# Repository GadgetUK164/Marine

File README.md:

<h1>Marine (Amber Replacement)</h1>
Marine is a modern CPLD replacement, designed to replace the Amber chip in the Commodore Amiga.
This project is based on the work of Matthias Heinrichs - AGA Multifix.
You can see his original project here:- https://gitlab.com/MHeinrichs/multifix-aga/-/tree/master

A massive thanks to Matthias for creating the AGA Multifix, and for allowing me to adapt to an Amber replacement.

<h1>License</h1>
This project is open source, and should not be sold commercially.

Do whatever you want with this, if you do it for private use and mention this work, and the AGA Multifix as origin.
If you want to make money out of this work, ask Matthias Heinrichs.
If you copy parts of this work to your project, mention the source.
If you use parts of this work for closed source, burn in hell and live in fear!

<h1>How Does It Work</h1>
It uses the magic code from the AGA Multifix to control the read resets, write resets, read enables and write enables of the Frame RAM and Line RAM contained on the Amiga 3000 motherboard.  It also works in the GBA1000 from Georg Braun.
JP1 and JP2 are added for future changes.   At the time of public release it supports NTSC Line RAM only.  It may be possible with a future firmware update, to use one of the jumpers to toggle between NTSC and PAL Line RAM.<br><br>   To my knowledge Amiga 3000 computers all shipped with NTSC Line RAM from the factory.  ie. uPD42101.   PAL RAM is uPD42102<br><br>
Note: There are different speeds of these RAM chips.  So far this has been tested working correctly with uPD42101-3 Line RAM.<br>
<ul>
<li>Official 3000 (Rev 9.x)</li>
<li>Re-Amiga 3000 (Rev 11)</li>
<li>GBA1000</li>
</ul>
Note: You could in theory use 2 x PAL Line RAM, and 2 x NTSC Line RAM chips.  The ones on the combined "path" need to be NTSC.<br><br>
In addition J481 on the 3000 motherboard (provided JP1 is closed) can be used to enable scanlines in progressive mode.  Before anyone asks, it's not practical to have scanlines in interlaced modes - additional pixel data is contained in interlaced.  In progressive, each scanline just gets output twice, so a black scanline for the odd scanlines makes sense!<br><br>
<h1>Important</h1>
The board currently fits into the PLCC footprint using turned pins.   It is recommended to remove the PLCC socket, and fit turned pin (female) strips to the motherboard.  Then fit turned pin (male) strips to the Marine PCB.<br><br>
I noticed that when testing PAL Interlaced on the Amiga 3000 using the default 74ALS74 (U480) which Commodore fitted to the motherboard, the video is not very sharp at all.  This can be improved massively by swappping U480 on the 3000 to a 74F74.  The GBA1000 already has a 74F74 in that location.
<br><br>
The RGB output levels to the Commodore Hybrid are at the 3.3v logic levels, and whilst testing has revealed the difference to be a negligble amount of effect on brightness, it may be an idea to fit a customised modern hybrid in place of HY480.
You can alter the bias resistors on a modern Hyrid replacement (eg. to 330 ohm, down from the original 470 ohm).  But in my opinion this is not required.  I've not done it on my 3000, and I honestly cannot see a difference to the output.  If I scope it, I am sure there will be a difference though!<br><br>
As mentioned above, use NTSC Line RAM (uPD42101-3).<br>
In future I might be able to support PAL Line RAM via a code change and use of JP2.

<h1>Repository Contents</h1>
KiCad 7.0 PCB Design Files & Schematics
<br>
ISE 14.7 VHD and pins files for Logic

<h1>Components Needed</h1>
<ul>
<li>Xilinx XC95144XL-10TQ100 CPLD</li>
<li>R1  0603 Resistor 10K</li>
<li>R2  0603 Resistor 10K</li>
<li>R3  0603 Resistor 10K</li>
<li>R4  0603 Resistor 10K</li>
<li>L1  0805 Ferrite (I went with 9ohm @ 100Mhz) - You could just fit 0ohm or 1ohm here I think!</li>
<li>U1  SOT-223 AMS1117 3.3V Regulator</li>
<li>C1  0805 MLC Capacitor 4.7uF 50V</li>
<li>C2  0805 MLC Capacitor 10uF  50V</li>
<li>C3  0805 MLC Capacitor 1uF   50V</li>
<li>C4  0805 MLC Capacitor 100nF 50V</li>
<li>2.54 pitch turned pin strips (female for motherboard, male for Marine)</li>
</ul>

<h1>Limitations</h1>
I offer no warranty on this design.  It works for me, and I am happy!
If you have a problem, I can investigate - but this is a hobby project.<br><br>
Super Hires will display, but not 100% correctly - it can look pretty good but a pixel will be missed every so often due to sampling into smaller RAM at a lower clock rate than required.  The RAM used on the Amiga 3000 cannot hold 1200 pixels of a scanline, so some sampling issues will be noticed when trying to display Super Hires.
I have tested many games and demos that use either interlaced or progressive and found no problems.<br><br>
Video modes supported by Super Denise (ECS) are not supported (as per Amber).
The bypass switch on the 3000 has been tested and works as per Amber original manual bypass.
J481 is not supported as per the original Amber, partly because I couldnt work out how it was used!  It now can be used to enable or disable scanlines in progressive display modes. (JP1 should be closed too enable scan lines - master enable)<br><br>
I found it harder to "dial in" regards the Amiga 3000 PLL adjustment (trim cap and resistor).  That was NOT the case with the Re-Amiga 3000, or the GBA1000.  PLL adjustment on those systems was much easier for me. <br><br>
NTSC interlaced display modes are definitely sharper than PAL interlaced ones, just marginally!  This could indicate that my timing is not spot on just yet!<br><br>
It may benefit from a re-design to add:-<br>
<br>
<ul>
<li>More decoupling on CPLD power pins?</li>
<li>Buffering of RGB output to TTL levels?</li>
<li>Schmitt Triggers on 14Mhz and 28Mhz inputs?</li>
<li>4 layer?</li>
<li>PLCC plug (separate interposer might be possible)?</li>
</ul>

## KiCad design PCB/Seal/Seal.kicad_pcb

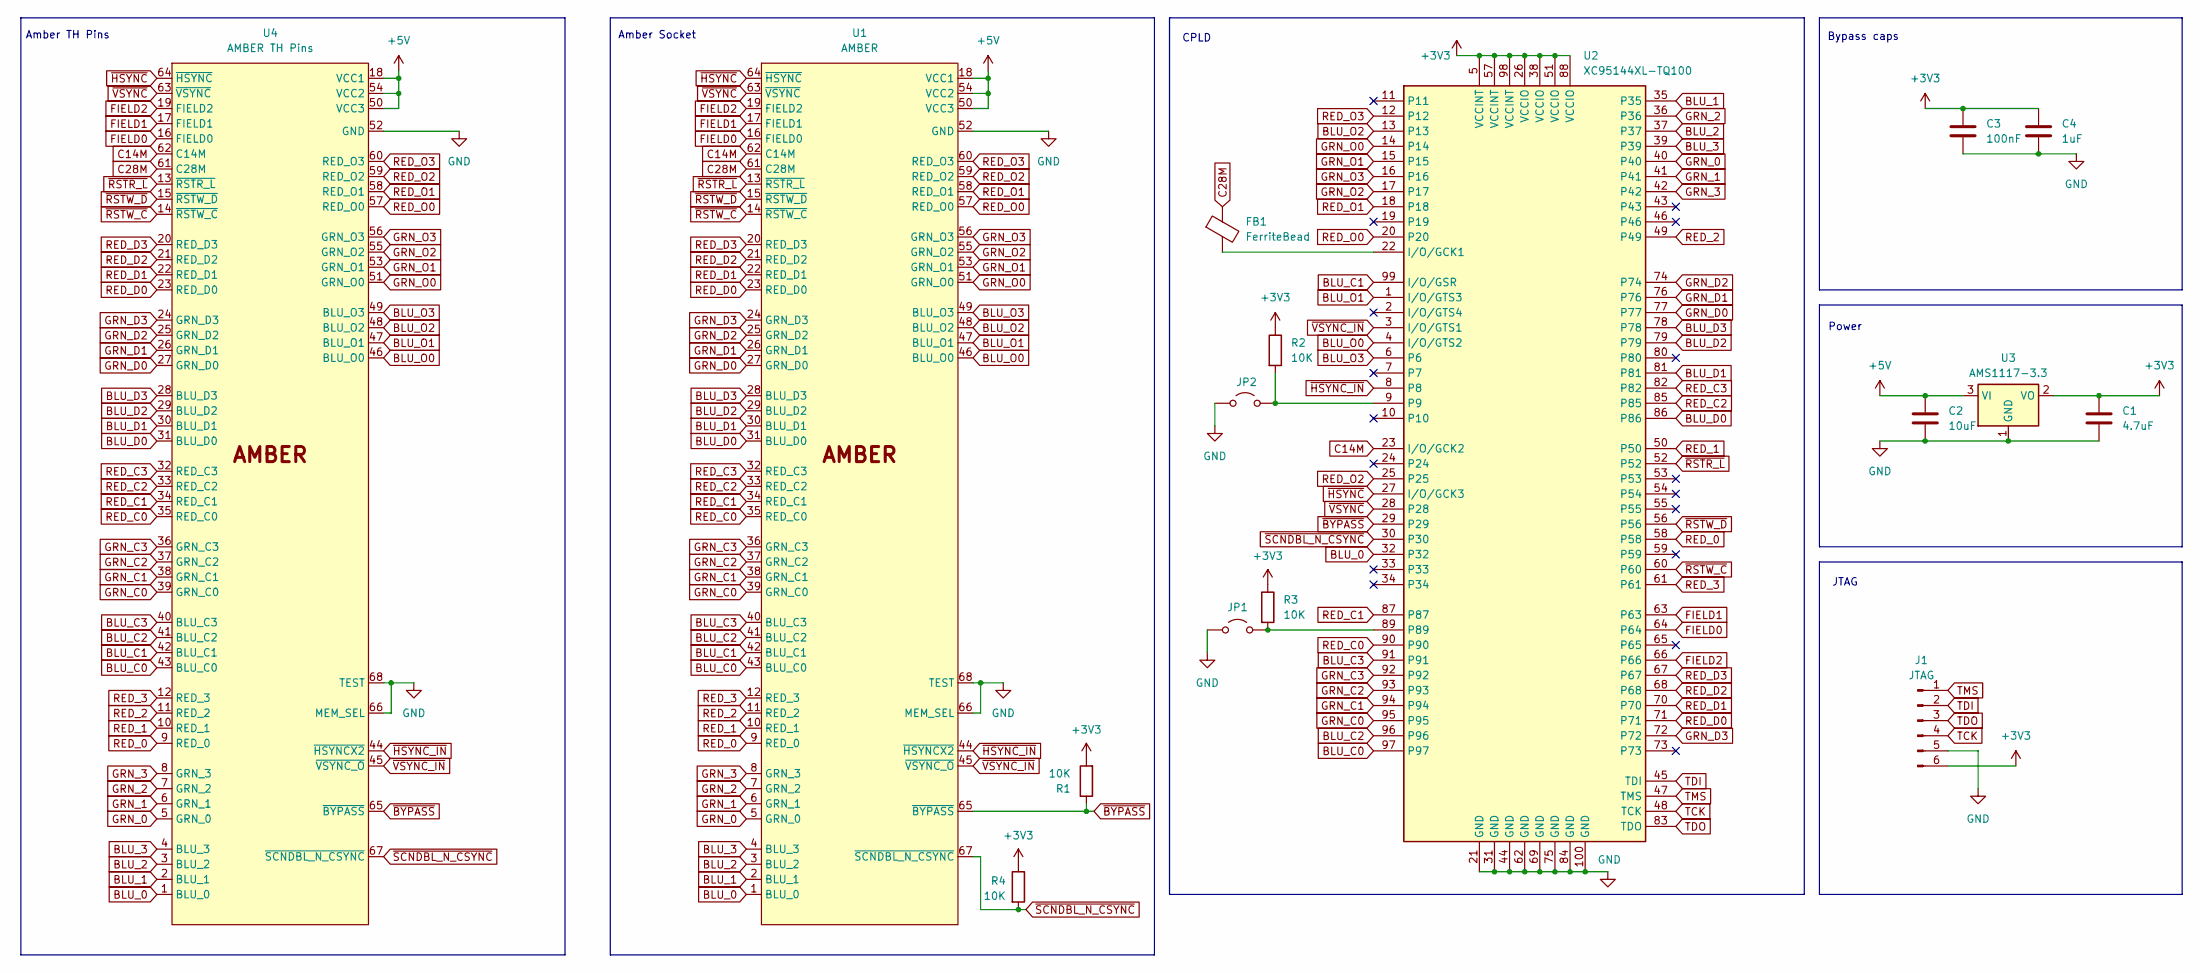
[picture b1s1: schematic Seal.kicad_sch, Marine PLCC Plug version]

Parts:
C1: 4.7uF; C_0603_1608Metric_Pad1.08x0.95mm_HandSolder; LCSC C19666
C2: 10uF; C_0603_1608Metric_Pad1.08x0.95mm_HandSolder; LCSC C96446
C3: 100nF; C_0603_1608Metric_Pad1.08x0.95mm_HandSolder; LCSC C14663
C4: 1uF; C_0603_1608Metric_Pad1.08x0.95mm_HandSolder; LCSC C15849
FB1: FerriteBead; L_0603_1608Metric_Pad1.05x0.95mm_HandSolder; LCSC C88974
J1: JTAG; PinHeader_1x06_P2.54mm_Vertical; LCSC C6332199
JP1, JP2: SolderJumper-2_P1.3mm_Open_RoundedPad1.0x1.5mm
R1, R2, R3, R4: 10K; R_0603_1608Metric_Pad0.98x0.95mm_HandSolder; LCSC C25804
U1: AMBER; APW9327_single_sided
U2: XC95144XL-TQ100; TQFP-100_14x14mm_P0.5mm; LCSC C45126
U3: AMS1117-3.3; SOT-223-3_TabPin2; LCSC C6186
U4: AMBER TH Pins; PLCC-68_TH_pin_holes

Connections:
+3V3: C1.1, C3.1, C4.1, J1.6, R1.2, R2.1, R3.1, R4.1, U2.5 (VCCINT), U2.26 (VCCIO), U2.38 (VCCIO), U2.51 (VCCIO), U2.57 (VCCINT), U2.88 (VCCIO), U2.98 (VCCINT), U3.2 (VO)
+5V: C2.1, U1.18 (VCC1), U1.50 (VCC3), U1.54 (VCC2), U3.3 (VI), U4.18 (VCC1), U4.50 (VCC3), U4.54 (VCC2)
BLU_0: U1.1 (BLU_0), U2.32, U4.1 (BLU_0)
BLU_1: U1.2 (BLU_1), U2.35, U4.2 (BLU_1)
BLU_2: U1.3 (BLU_2), U2.37, U4.3 (BLU_2)
BLU_3: U1.4 (BLU_3), U2.39, U4.4 (BLU_3)
BLU_C0: U1.43 (BLU_C0), U2.97, U4.43 (BLU_C0)
BLU_C1: U1.42 (BLU_C1), U2.99 (I/O/GSR), U4.42 (BLU_C1)
BLU_C2: U1.41 (BLU_C2), U2.96, U4.41 (BLU_C2)
BLU_C3: U1.40 (BLU_C3), U2.91, U4.40 (BLU_C3)
BLU_D0: U1.31 (BLU_D0), U2.86, U4.31 (BLU_D0)
BLU_D1: U1.30 (BLU_D1), U2.81, U4.30 (BLU_D1)
BLU_D2: U1.29 (BLU_D2), U2.79, U4.29 (BLU_D2)
BLU_D3: U1.28 (BLU_D3), U2.78, U4.28 (BLU_D3)
BLU_O0: U1.46 (BLU_O0), U2.4 (I/O/GTS2), U4.46 (BLU_O0)
BLU_O1: U1.47 (BLU_O1), U2.1 (I/O/GTS3), U4.47 (BLU_O1)
BLU_O2: U1.48 (BLU_O2), U2.13, U4.48 (BLU_O2)
BLU_O3: U1.49 (BLU_O3), U2.6, U4.49 (BLU_O3)
C14M: U1.62 (C14M), U2.23 (I/O/GCK2), U4.62 (C14M)
C28M: FB1.1, U1.61 (C28M), U4.61 (C28M)
FIELD0: U1.16 (FIELD0), U2.64, U4.16 (FIELD0)
FIELD1: U1.17 (FIELD1), U2.63, U4.17 (FIELD1)
FIELD2: U1.19 (FIELD2), U2.66, U4.19 (FIELD2)
GND: C1.2, C2.2, C3.2, C4.2, J1.5, JP1.1 (A), JP2.1 (A), U1.52 (GND), U1.66 (MEM_SEL), U1.68 (TEST), U2.21 (GND), U2.31 (GND), U2.44 (GND), U2.62 (GND), U2.69 (GND), U2.75 (GND), U2.84 (GND), U2.100 (GND), U3.1 (GND), U4.52 (GND), U4.66 (MEM_SEL), U4.68 (TEST)
GRN_0: U1.5 (GRN_0), U2.40, U4.5 (GRN_0)
GRN_1: U1.6 (GRN_1), U2.41, U4.6 (GRN_1)
GRN_2: U1.7 (GRN_2), U2.36, U4.7 (GRN_2)
GRN_3: U1.8 (GRN_3), U2.42, U4.8 (GRN_3)
GRN_C0: U1.39 (GRN_C0), U2.95, U4.39 (GRN_C0)
GRN_C1: U1.38 (GRN_C1), U2.94, U4.38 (GRN_C1)
GRN_C2: U1.37 (GRN_C2), U2.93, U4.37 (GRN_C2)
GRN_C3: U1.36 (GRN_C3), U2.92, U4.36 (GRN_C3)
GRN_D0: U1.27 (GRN_D0), U2.77, U4.27 (GRN_D0)
GRN_D1: U1.26 (GRN_D1), U2.76, U4.26 (GRN_D1)
GRN_D2: U1.25 (GRN_D2), U2.74, U4.25 (GRN_D2)
GRN_D3: U1.24 (GRN_D3), U2.72, U4.24 (GRN_D3)
GRN_O0: U1.51 (GRN_O0), U2.14, U4.51 (GRN_O0)
GRN_O1: U1.53 (GRN_O1), U2.15, U4.53 (GRN_O1)
GRN_O2: U1.55 (GRN_O2), U2.17, U4.55 (GRN_O2)
GRN_O3: U1.56 (GRN_O3), U2.16, U4.56 (GRN_O3)
unnamed: JP1.2 (B), R3.2, U2.89
unnamed: JP2.2 (B), R2.2, U2.9
unnamed: FB1.2, U2.22 (I/O/GCK1)
RED_0: U1.9 (RED_0), U2.58, U4.9 (RED_0)
RED_1: U1.10 (RED_1), U2.50, U4.10 (RED_1)
RED_2: U1.11 (RED_2), U2.49, U4.11 (RED_2)
RED_3: U1.12 (RED_3), U2.61, U4.12 (RED_3)
RED_C0: U1.35 (RED_C0), U2.90, U4.35 (RED_C0)
RED_C1: U1.34 (RED_C1), U2.87, U4.34 (RED_C1)
RED_C2: U1.33 (RED_C2), U2.85, U4.33 (RED_C2)
RED_C3: U1.32 (RED_C3), U2.82, U4.32 (RED_C3)
RED_D0: U1.23 (RED_D0), U2.71, U4.23 (RED_D0)
RED_D1: U1.22 (RED_D1), U2.70, U4.22 (RED_D1)
RED_D2: U1.21 (RED_D2), U2.68, U4.21 (RED_D2)
RED_D3: U1.20 (RED_D3), U2.67, U4.20 (RED_D3)
RED_O0: U1.57 (RED_O0), U2.20, U4.57 (RED_O0)
RED_O1: U1.58 (RED_O1), U2.18, U4.58 (RED_O1)
RED_O2: U1.59 (RED_O2), U2.25, U4.59 (RED_O2)
RED_O3: U1.60 (RED_O3), U2.12, U4.60 (RED_O3)
TCK: J1.4, U2.48 (TCK)
TDI: J1.2, U2.45 (TDI)
TDO: J1.3, U2.83 (TDO)
TMS: J1.1, U2.47 (TMS)
~BYPASS: R1.1, U1.65 (~BYPASS), U2.29, U4.65 (~BYPASS)
~HSYNC_IN: U1.44 (~HSYNCX2), U2.8, U4.44 (~HSYNCX2)
~HSYNC: U1.64 (~HSYNC), U2.27 (I/O/GCK3), U4.64 (~HSYNC)
~RSTR_L: U1.13 (~RSTR_L), U2.52, U4.13 (~RSTR_L)
~RSTW_C: U1.14 (~RSTW_C), U2.60, U4.14 (~RSTW_C)
~RSTW_D: U1.15 (~RSTW_D), U2.56, U4.15 (~RSTW_D)
~SCNDBL_N_CSYNC: R4.2, U1.67 (~SCNDBL_N_CSYNC), U2.30, U4.67 (~SCNDBL_N_CSYNC)
~VSYNC_IN: U1.45 (~VSYNC_O), U2.3 (I/O/GTS1), U4.45 (~VSYNC_O)
~VSYNC: U1.63 (~VSYNC), U2.28, U4.63 (~VSYNC)

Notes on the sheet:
JTAG
Amber TH Pins
CPLD
Bypass caps
Amber Socket
Power

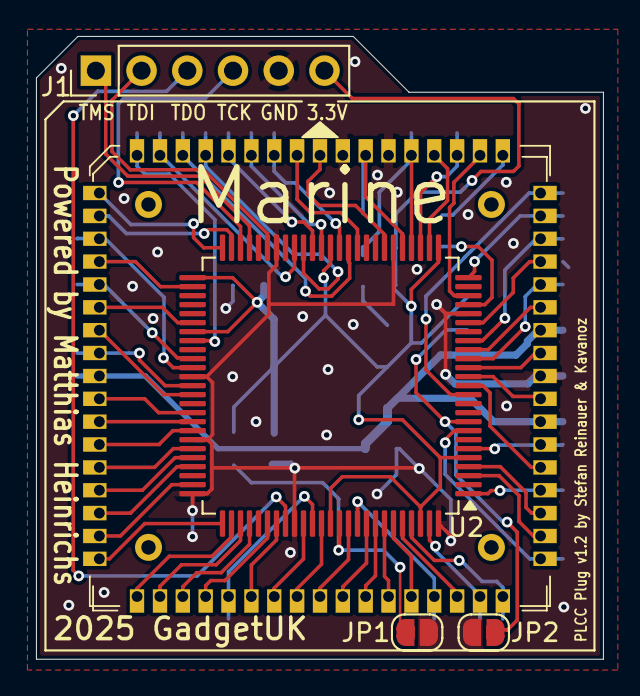
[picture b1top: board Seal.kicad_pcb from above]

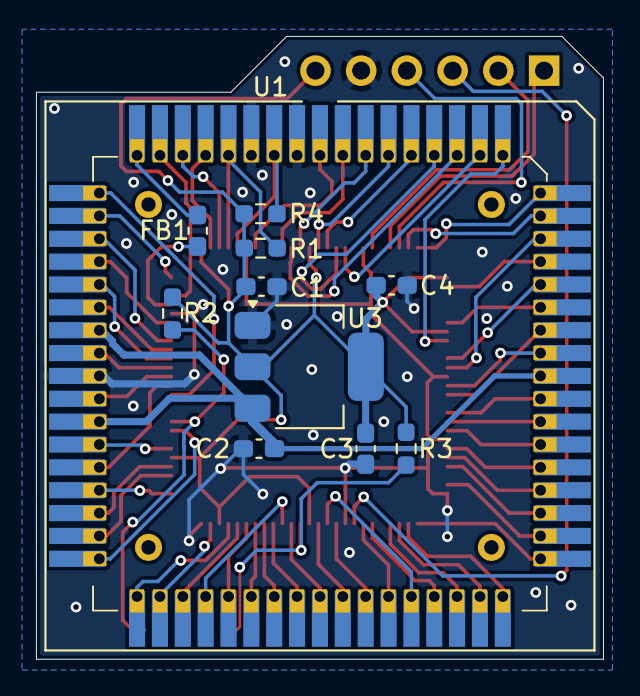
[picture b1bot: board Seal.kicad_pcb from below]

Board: 2 copper layers, 31.5 x 34.6 mm, 16 parts (11 on the bottom side), 72 nets.

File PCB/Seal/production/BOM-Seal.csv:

Comment,Designator,Footprint,LCSC,Quantity
100nF,C3,C_0603_1608Metric_Pad1.08x0.95mm_HandSolder,C14663,1
10K,"R1,R2,R3,R4",R_0603_1608Metric_Pad0.98x0.95mm_HandSolder,C25804,4
10uF,C2,C_0603_1608Metric_Pad1.08x0.95mm_HandSolder,C96446,1
1uF,C4,C_0603_1608Metric_Pad1.08x0.95mm_HandSolder,C15849,1
4.7uF,C1,C_0603_1608Metric_Pad1.08x0.95mm_HandSolder,C19666,1
AMS1117-3.3,U3,SOT-223-3_TabPin2,C6186,1
FerriteBead,FB1,L_0603_1608Metric_Pad1.05x0.95mm_HandSolder,C88974,1
JTAG,J1,PinHeader_1x06_P2.54mm_Vertical,C6332199,1
XC95144XL-TQ100,U2,TQFP-100_14x14mm_P0.5mm,C45126,1

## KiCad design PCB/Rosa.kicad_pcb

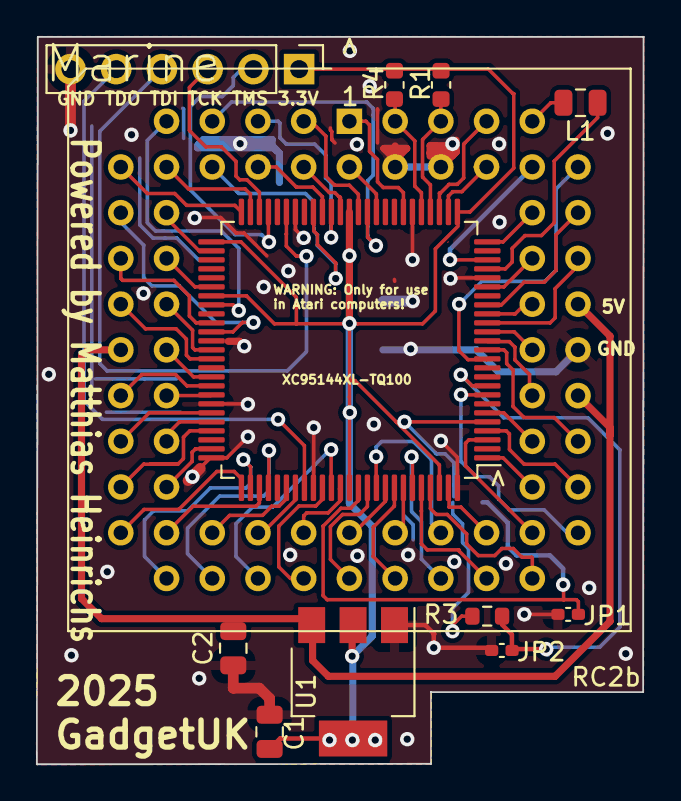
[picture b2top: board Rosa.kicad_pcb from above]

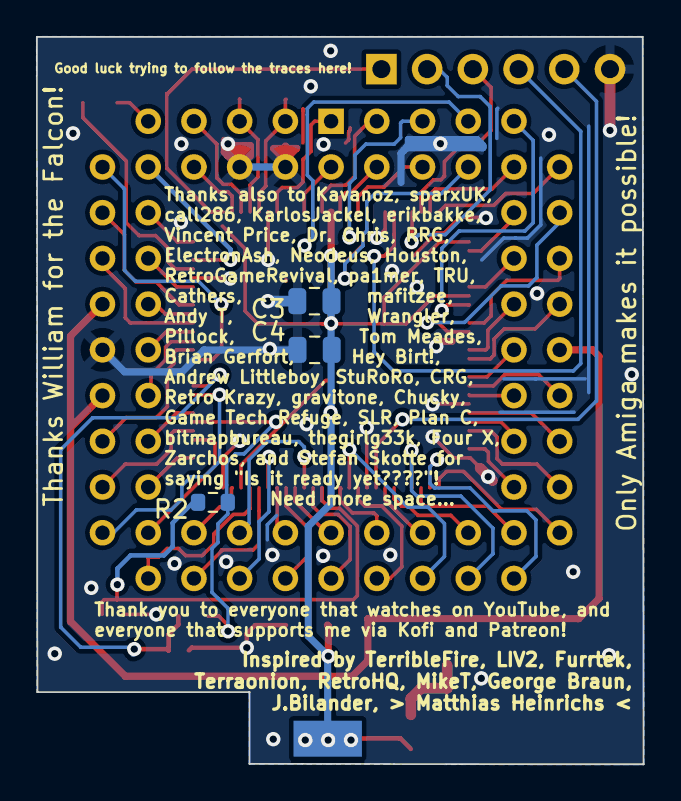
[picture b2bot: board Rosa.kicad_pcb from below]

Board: 2 copper layers, 33.7 x 40.4 mm, 13 parts (3 on the bottom side), 2 nets.

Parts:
                              Marine: Amber
C1: C1; C_0805_2012Metric
C2: C2; C_0805_2012Metric
C3, C4: C_0805_2012Metric
JP1, JP2: C_0402_1005Metric_Pad0.74x0.62mm_HandSolder
L1: L1; C_0805_2012Metric
R1, R4: L_0603_1608Metric
R2, R3: R_0603_1608Metric
U1: SOT-223

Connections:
GND: Marine.GND, C1.2, C2.1, C3.1, C4.1, JP1.1, JP2.1, U1.GND
VCC_3: C1.1, C3.2, C4.2, R1.1, U1.3V3

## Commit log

2025-06-12 Initial public release
2025-06-12 Initial version for public release
2025-08-27 Update README.md
    RC2 tested all OK.
2025-09-01 Add files via upload
    Partial schematics updated. Lacks most of the IO pin routing.
2025-10-31 Update Rosa.kicad_pcb
    Additional credit.
2026-02-21 PCB: Move Rosa PCB to its own subdirectory
    And drop fp-info-cache, it is not needed / wanted.
2026-02-22 Add a Makefile for the VHDL code
    This lets us compile the VHDL into a JED on the command line
2026-02-22 RTL: Add PAL Line RAM (uPD42102) support via JP2
    The line buffer read/write reset timing was previously derived from
    TV_MODE (the detected video standard), which implicitly assumed NTSC
    Line RAM (uPD42101, 910 words). This fails with PAL Line RAM
    (uPD42102, 908 words) because the mid-line reset point must match the
    physical RAM capacity boundary (454 vs 455 half-line clocks), not the
    video standard.
2026-02-22 Add Seal PCB (PLCC plug version)
